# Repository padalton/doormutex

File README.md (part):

# doormutex 🚦

*A mutex for your door.*

**A traffic light for my basement office.** From the hallway the family can see whether it's worth coming downstairs:
🔴 **red** = meeting, please don't disturb · 🟡 **yellow** = working, come in if it's important · 🟢 **green** = come in · ⚫ **off** = not in the office.

The state is detected automatically (microphone/camera, Google Calendar, working hours, screen lock) and can be overridden at any time from a KDE widget, a Stream Deck or the web UI. Open source & open hardware: software, firmware, PCB (KiCad) and a 3D-printed enclosure (OpenSCAD).

> **Status: early development.** This README is the project definition and feature set (as of 2026-10-30). The repo is public from day one so anyone can follow the project as it grows. Software: [`hub/`](hub/) (with web UI), [`companion/`](companion/), [`plasmoid/`](plasmoid/), [`streamdeck/`](streamdeck/).
>
> More documents: [Breadboard prototype & parts list](docs/breadboard.md) · [Wiring the breadboard](docs/wiring.md) · [Development setup](docs/dev-setup.md) · [Google Calendar](docs/google-calendar.md) · [iPhone & Shortcuts](docs/apple-shortcuts.md) · [Android](docs/android.md) · [Hub](hub/README.md) · [API (OpenAPI)](api/openapi.yaml) · [Translating](TRANSLATING.md)

## Signals

One traffic light, three chambers, just like on the road: red on top, yellow in the middle, green at the bottom. The position tells the meaning, even without telling the colours apart.

| Light | State | Meaning | E-ink sign (example) |
|---|---|---|---|
| 🔴 red | `dnd` | Meeting – please don't come in | "Meeting · until 14:30" |
| 🟡 yellow | `working` | Working – only if it's important | "Working · next meeting 15:00" |
| 🟢 green | `free` | Come in! | "Free · next appointment tomorrow 09:00" |
| ⚫ off | `away` | Not in the office (PC locked or off) | "Not in the office" |

**Phases**, modelled on the Austrian road traffic regulations (StVO § 38):

| Light | Phase | When |
|---|---|---|
| 🟢 blinking | **Last call** | before a meeting, coming from green – "quick, I'm in a meeting soon" |
| 🔴 / 🟡 alternating | **Last call from yellow** | before a meeting, coming from yellow. The StVO has no such signal, and blinking yellow is taken by the fault |
| 🔴 + 🟡 | **Ending soon** | before a meeting ends and yellow or green follows. In the StVO, red+yellow means: stop, green is coming |
| 🟡 blinking | **Fault** | hub or Wi-Fi gone, data too old, or the companion went silent without signing off. Blinking yellow means "caution" in the StVO |
| off + "battery empty" | **Battery empty** | cut-off threshold reached |

**Timing:** by default the phases follow the StVO – green blinks four times, yellow shows ≈ 3 s before red, red+yellow ≈ 1–2 s before green. That's authentic, but over in seconds. A switch per phase (config and web UI) turns it into a real warning with a lead time instead, e.g. 3 or 5 minutes.

### E-ink sign

A small e-ink display sits below the light. It shows **absolute times instead of a countdown** ("until 14:30" rather than "23 min left"). So the content only changes when the state changes: no motion sensor needed, no power while idle.

1.54″, 200 × 200 pixels, black and white – rendered by the hub (frames from the tests, actual size). E-ink has no colour, so the status is a big word plus a symbol: ⛔ do not disturb, 🕓 working, ✓ come in, ☾ not here, ⚠ fault. The light already shows the colour; the sign adds the small print, readable right in front of the light.

Content: status, until when, the reason (event kind such as "video call", never a title) or the message, the next free time, the time of the last change and the battery. The frame only changes when its content does, so the panel isn't refreshed for nothing. English and German (per profile, setting `eink_language`).

## Feature set

### Must – v1

- **Traffic light hardware:** three chambers (red/yellow/green), ESP32-C6, Wi-Fi + MQTT, 18650 cell with safe charging electronics, USB-C for charging *and* permanent power
- **E-ink sign:** until when, what's next, reason, battery
- **Enclosure as a miniature traffic light** (OpenSCAD) with a removable wall mount
- **Automatic detection:**
  - microphone or camera in use → red
  - Google Calendar → red or yellow, by rules
  - working hours (incl. Austrian public holidays) → yellow
  - PC locked → off
  - otherwise → green
- **Manual override with duration:** from 15 min to "until end of work day", "until the next automatic change" or indefinite; "auto" resets
- **KDE Plasma widget** (panel and desktop): see the detected state and its reason, override with a time, pomodoro
- **Desktop notification** on every state change
- **Last call** and **failsafe** (see Signals)
- **Home Assistant via MQTT discovery:** state, state-change event, current slot, next free slot, battery
- **Hub as a Docker container** in the homelab

### Should

- **Ending soon** phase (red+yellow)
- **Stream Deck XL** as a control panel
- **Flashing and Wi-Fi setup in the browser** (ESP Web Tools + Improv), OTA updates
- **Automatic brightness** via light sensor, night dimming
- **Battery runtime estimate** in HA
- **Profiles:** several people and lights on one hub, each with its own rules, calendars and tokens
- **Room mode** for people without a PC companion – a teenager's room, the parents' bedroom or living room: controlled by phone (web app, Apple Shortcuts), web UI or Home Assistant, and through HA by voice via Alexa or Google Home (see [Profiles & room mode](#profiles--room-mode))

### Could

- **Matter over Wi-Fi** (uncertified, without the logo): Apple Home, Google Home, Alexa and HA directly, next to MQTT. Matter has no traffic-light device type, so each state becomes an on/off endpoint (mutually exclusive)
- Generic **webhook signals**, e.g. for Claude Code (see below)
- **ESPHome example config** for builds on mains power ("bring your own lamp")
- **Prometheus metrics** and a Grafana dashboard (meeting statistics)
- **Wi-Fi 6 TWT** on the ESP32-C6 for longer battery life, if the router supports it
- Companion for Windows/macOS, GNOME extension
- "Tell me when free" push (ntfy) – for families who don't just text anyway

### Won't – on purpose

| Idea | Why not |
|---|---|
| A second light at the basement door | The decision is made at the top of the stairs – one light is enough |
| Knock button / back channel | The family texts on WhatsApp anyway |
| Dedicated control desk ("signal box") | Stream Deck XL + widget cover it |
| Motion / mmWave sensor on the device | The LEDs stay on (visible from the hallway) and the e-ink only changes with the state. An mmWave sensor (~70–80 mA) would drain the battery in 1–2 days |
| ESP-NOW / Thread / Zigbee | Wi-Fi is good everywhere, MQTT broker and HA exist – Wi-Fi is simpler |
| Countdown on LEDs | too much power – the e-ink shows absolute times |
| Work/private detection via folder paths, VPN etc. | doesn't fit: everything runs on one machine, paths are personal |
| Ready-made HA automations | entities + triggers only; everyone builds their own automations |
| RGB LEDs (WS2812) | real single colours, position encodes meaning; WS2812 draw current even when "off" |

## Architecture

```mermaid
flowchart LR
  subgraph desk["Desk (KDE Plasma)"]
    comp["Companion<br/>mic · camera · lock<br/>notifications"]
    widget["Plasma widget<br/>state · override · pomodoro"]
    deck["Stream Deck XL<br/>OpenDeck plugin"]
  end
  subgraph lab["Homelab (Docker)"]
    hub["Hub<br/>rule engine · API · web UI<br/>e-ink rendering"]
    mqtt[("MQTT broker")]
    ha["Home Assistant"]
  end
  gcal["Google Calendar"] --> hub
  comp -->|signals + heartbeat| hub
  hub -->|state changes| comp
  widget <--> hub
  deck <--> hub
  hub <--> mqtt
  mqtt <--> ha
  mqtt <-->|Wi-Fi| light["🚦 Traffic light at the stairs<br/>ESP32-C6 · e-ink · 18650"]
  ha -.->|your own automation| hue["Hue stair light"]
```

**Principle: smart hub, dumb light.** The hub decides everything – state, phase, blink pattern, e-ink content – and publishes it via MQTT. The light only displays, reports telemetry and switches to "fault" by itself when the hub goes quiet.

| Component | Tech | Job |
|---|---|---|
| Hub | Go, Docker, SQLite | Rule engine, calendar, working hours, REST/SSE API, web UI, MQTT + HA discovery, e-ink rendering |
| Companion | Go, systemd user service | Microphone/camera (PipeWire), screen lock, desktop notifications, OAuth helper |
| Plasma widget | QML (Plasma 6) | State, override, pomodoro |
| Stream Deck plugin | Go, Elgato SDK protocol | Control panel on the Stream Deck XL (OpenDeck, Elgato app) |
| Firmware | C, ESP-IDF | Wi-Fi power saving, MQTT, LEDs, e-ink, battery |
| Project homepage | GitHub Pages (static) + own domain | Required for Google's OAuth branding (description, privacy policy, terms), plus docs, web flasher (ESP Web Tools needs HTTPS) and the OAuth redirect relay. No backend, no user data |
| PCB | KiCad | ESP32-C6, charging, LED and e-ink drivers – assembled by JLCPCB |
| Enclosure | OpenSCAD (plain, Manifold backend) | Miniature traffic light, magnet foot/side plate, later a removable wall mount |

Home Assistant is not a separate component: the hub announces its entities via MQTT discovery and HA picks them up.

**Why Go?** One static binary per component, tiny Docker images, good libraries for MQTT, D-Bus and Google APIs – and the companion can later be cross-compiled for Windows/macOS.

**API first:** the OpenAPI spec in [`api/openapi.yaml`](api/openapi.yaml) is the contract between hub, companion, widget and Stream Deck plugin. A test keeps spec and router in sync.

| Endpoint | Purpose |
|---|---|
| `GET /api/v1/status` | current state incl. reason, slot, next free slot |
| `GET /api/v1/timeline?from=…&to=…` | planned slots from calendar, working hours and timers |
| `PUT` / `DELETE /api/v1/override` | set an override (status + duration or end) / clear it |
| `PUT` / `DELETE /api/v1/pomodoro` | start / stop a pomodoro timer (work phase red by default; setting `pomodoro_work_status` or `work_status` per request for yellow) |
| `POST /api/v1/signals/companion` | companion heartbeat (microphone, camera, lock) and goodbye before shutdown/suspend |
| `POST` / `DELETE /api/v1/signals/{source}` | webhook signals with TTL |
| `GET /api/v1/events` | live updates (Server-Sent Events) |
| `GET /api/v1/profiles` | profiles the token may see, with their state |
| `GET` / `PUT /api/v1/settings` | light per calendar event kind, warning timing (saved, overrides the config) |
| `PUT` / `DELETE /api/v1/message` | e-ink message |
| `GET /api/v1/eink.png`, `GET /api/v1/eink.bin` | the e-ink frame as a preview image / packed for the panel (5000 bytes, SSD1681 layout), with ETag |
| `GET /api/v1/calendar`, `GET /api/v1/history` | calendar account health, recent status changes |

## State logic

Every source contributes a *claim*: status, priority and validity. The best valid claim wins.

| Prio | Source | Result | Details |
|---|---|---|---|
| 1 | Microphone or camera in use | `dnd` | counts after ≥ 10 s (debounce), holds for 2 min (reconnects, chat after the call) |
| 2 | PC locked, shut down or suspended | `away` | the companion signs off; silence without a goodbye is a fault (see below) |
| 3 | Manual override (widget, Stream Deck, web UI, phone, HA) or pomodoro | any | always ends: after a duration, "until the event ends", "until end of work day", "until the next automatic change" – or explicitly indefinite |
| 4 | Calendar event | by event kind | see [Google Calendar](#google-calendar) |
| 5 | Working hours | `working` | weekly plan, public holidays, extra days off |
| 6 | Webhook signals (optional) | usually `working` | with TTL |
| 7 | Default | `free` | – |

- **Microphone/camera beat everything,** including a manual override: a spontaneous Slack or Teams call turns the light red at once. The override isn't cleared and applies again after the call.
- **Microphone/camera beat the lock screen:** nobody locks the PC by hand during a call. But in a meeting where you only listen, you don't touch the mouse, and after a few minutes the screen locks itself. It stays red anyway.
- **Locking beats the override:** a nerd only locks the PC when leaving the desk. The override isn't cleared either; after unlocking it applies again while it's still valid.
- **Heartbeats:** the companion reports every 30 s and signs off on shutdown, suspend and lock (logind). If it is silent for 90 s *without* signing off (crash, killed), the light shows a fault (yellow blinks) until the end of the work day, then off.
- **Public holidays and days off** only remove the working hours. Calendar events still count: PC on with meetings on a holiday → red as usual (holiday workers, self-employed); PC on without events → green; PC off → off.
- **Failsafe on the light:** hub offline (MQTT Last Will) or state too old → yellow blinks.
- **Planning ahead:** the hub knows the future (calendar + working hours). From it, it computes the current slot, the next change and the next free slot – for the e-ink, the widget and HA.
- **Unknown end:** a call without a calendar entry or a locked screen has no known end. Then `until` and `next_free` are `null` instead of a guess. If a calendar meeting is running during a call, the call is assumed to end with the meeting.

## Profiles & room mode

One hub, several **profiles** – one per person and light. Each profile has its own rules, calendars, working hours, MQTT topics and API tokens. A token only controls its own profile: the teenager's phone can't switch the office light.

**Room mode** is a profile without a PC companion and usually without a calendar. It is for everyone who isn't the nerd in the basement: a teenager's room, the parents' bedroom or living room.

- **Controls:** phone, web UI and Home Assistant – and through HA by voice via Alexa or Google Home.
- **No companion required:** the light shows what was set last; when that ends, it falls back to the profile's default (e.g. off).
- **The e-ink shows a short message** ("Gaming until 21:00").
- **The office profile can also run without a companion,** controlled only via HA (light and message) – for setups where the companion can't run.

**Configuration** (see [`hub/config.example.yaml`](hub/config.example.yaml)):

```yaml
profiles:
  - id: office
    mode: office # companion, calendar, working hours
  - id: teen
    name: Teen room
    mode: room # no companion, no working hours, off by default
```

```bash
doormutex-hub token create teen-phone teen               # works only for profile "teen"
doormutex-hub token create widget                        # all profiles, choose with ?profile=
doormutex-hub token create couch teen office --read-only # only looks, never switches
```

The API serves the token's first profile without any extra parameter, so the same client works for every profile. `GET /api/v1/profiles` lists the profiles a token may see, `GET /api/v1/me` its role. A **read-only** token sees the state, the timeline, the history and the event stream, and nothing else – for a phone on the couch or a display in the kitchen. Tokens can also be created in the web UI: *Settings → Add a phone* shows a QR code for the phone.

Where room mode runs for people *without* a homelab (no Docker, no HA) is still open – see [open questions](#open-questions).

## Signal sources

### Companion (Linux)

Implemented in [`companion/`](companion/) – install as a systemd user service, see its README.

- **Microphone:** PipeWire capture streams (`media.class = Stream/Input/Audio`) in state "running". Ignored:
  - level meters (pavucontrol, the Plasma volume applet)
  - recordings of outputs (monitor sources, e.g. screen recording)
  - apps on a configurable ignore list
- **Camera:** open `/dev/video*` devices and PipeWire video streams.
- **Screen lock:** logind `LockedHint` of the user's graphical session (a systemd user service has no session of its own).
- **Goodbye:** before suspend and shutdown (logind delay inhibitor) and when the service stops; silence without a goodbye is a fault.
- **Notifications** on every state change, with the reason ("🔴 microphone in use – Firefox") and quick actions ("wrong detection", "clear override").
- **Reference setup:** CachyOS, KDE Plasma 6 (Wayland), PipeWire.

### Google Calendar

- **Connection:** Google Calendar API (recommended: near real time, provides `eventType`, attendees and conference links) or the secret iCal address (simpler, but sometimes heavily delayed).
- **Several Google accounts per profile,** e.g. private and work: each account has its own sign-in and refresh token, and any number of calendars per account.
- **Mirrored blockers:** in the reference setup HubSpot's "book a meeting" page reads the private calendar, so an Apps Script copies work events into it as blockers (the day job comes first). With both accounts connected the hub would see every work meeting twice. The script therefore marks its copies (`extendedProperties.private`), and the hub ignores marked copies when the source account is connected. If the work account can't be connected (e.g. the employer blocks third-party apps), the script can write the event kind into the mark instead, and the hub reads the kind from the copy.
- **Event kinds and default lights** – the light per kind can be changed in the web UI:

  | Kind | Detected via | Default |
  |---|---|---|
  | Video call | Google Meet: `conferenceData` (`hangoutsMeet`); Zoom, Teams, Webex, Jitsi: conference add-on or link in location/description | 🔴 `dnd` |
  | Focus time | `eventType: focusTime` | 🟡 `working` |
  | Out of office, timed | `eventType: outOfOffice` | 🔴 `dnd` – in the reference setup private appointments are blocked as OOO in the work calendar. If the PC is locked, the light is off anyway |
  | Out of office, all day | `eventType: outOfOffice`, all-day | day off (vacation): no working hours that day |
  | Other event | – | 🟡 `working` – e.g. a phone call on the mobile, which the companion can't see |
  | Tentative | invitation answered "maybe" or not answered yet (`responseStatus` `tentative` / `needsAction`) | 🟡 `working`, whatever the kind – or "like the kind", or ignored |
  | Ignored | working location, birthdays, other all-day events, events marked "free", declined events | – |

- **Overlapping events:** the strictest status wins (`dnd` before `working`), not the one that started last.
- **Calendar and microphone/camera complement each other:** a call known from the calendar gives the last call ahead of time; microphone/camera catch spontaneous calls and always win.
- **Focus time and out of office only exist in Google Workspace accounts** and only on primary calendars – in a private Gmail calendar there are plain events only.
- **Privacy:** location and description are only read to find video links; titles and contents are never stored or shown. Before connecting a work account, check the employer's IT policy.
- **Set-up:** [docs/google-calendar.md](docs/google-calendar.md) – OAuth client, sign-in from the web UI (*Settings → Calendar accounts*, through the redirect relay on doormutex.org) or with `doormutex-companion google login <account>` (browser on the desktop, no copy and paste; `doormutex-hub google login` for headless set-ups), mirrored copies. Refresh tokens are stored encrypted. `GET /api/v1/calendar` shows the health of every account.

#### Google sign-in for self-hosters

Two separate problems:

1. **Long-lived tokens.** While an OAuth app is in "Testing", refresh tokens expire after 7 days. To **publish** the app, the Google Auth Platform requires a complete branding page: homepage, privacy policy, terms of service and an authorized domain. The homepage must describe the app; a bare login page is not enough. For verification by Google you must also prove that you own the domain (Search Console). → **Without a real project homepage there is no long-term operation.**
2. **Redirect.** Every installation runs its hub under a different address, usually without public HTTPS. Web clients need an HTTPS redirect to a public domain. Desktop clients are the exception: they may redirect to loopback (`127.0.0.1`). Google does not allow the device flow ("enter a code on another device") for calendar scopes.

**Plan:**

- **Project homepage with its own domain** (GitHub Pages + custom domain, verified in Search Console): description, logo, screenshots, privacy policy, terms of service, docs and web flasher.
- **Stage 1 – for the reference build:** an own OAuth client whose branding points to the project homepage. It can then be published and the 7-day limit is gone. Until verification Google shows a warning at sign-in and caps unverified apps at 100 users.
- **Stage 2 – for everyone else:** a **shared project OAuth client**, verified by Google. `calendar.events.readonly` is a "sensitive" scope, not a "restricted" one: it needs a justification and a demo video, but no paid security assessment. After that, nobody needs their own Google Cloud console.
  - **Sign-in via the companion:** client type "desktop app", loopback redirect to `127.0.0.1`. Google explicitly does not treat the client secret of installed apps as a secret, so it may live in open-source code.
  - **Sign-in via the web UI without companion:** a **redirect relay** on the homepage, modelled on `my.home-assistant.io` – ✅ built for own clients (a second, "web application" client next to the desktop one). Google redirects to `https://doormutex.org/oauth/`; the static page forwards code and `state` only to the hub this browser started the sign-in from, which it stored locally before (a new hub needs a confirmation). The target never comes from the callback's URL parameters, otherwise the relay would be an open redirect. Still open for the shared client: web clients need the client secret for every token refresh in the hub, so it would be in every installation. To be checked before stage 2 starts.
- **Fallback without OAuth:** the calendar's secret iCal address – without `eventType` and attendees, and Google sometimes updates the feed with a long delay.

### Working hours

Weekly plan (e.g. Mon–Fri 08:00–17:00), public holidays per country (Austria built in), extra days off from the config, vacation and absence from the calendar.

### Webhooks (optional) – e.g. Claude Code

Any tool can set a claim with a TTL via `POST /api/v1/signals/<name>`. Example of a Claude Code hook in `~/.claude/settings.json`:

```json
{
  "hooks": {
    "UserPromptSubmit": [
      {
        "hooks": [
          {
            "type": "command",
            "command": "curl -fsS -m 2 -X POST \"$DOORMUTEX_URL/api/v1/signals/claude\" -H \"Authorization: Bearer $DOORMUTEX_TOKEN\" -d '{\"status\":\"working\",\"ttl\":\"30m\"}' || true"
          }
        ]
      }
    ]
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
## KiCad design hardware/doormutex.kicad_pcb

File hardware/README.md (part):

<!--
SPDX-FileCopyrightText: 2026 The doormutex contributors
SPDX-License-Identifier: CERN-OHL-S-2.0
-->

# Hardware

The KiCad project for PCB v1 (milestone M1b, after the [breadboard prototype](../docs/breadboard.md)): schematic, layout and the JLCPCB order files, all generated by scripts from one netlist. Not built yet. The design has been checked against the data sheets once ([what the review changed](#review-before-the-first-order)); [two things](#check-before-ordering) are left that need the e-paper module in hand and JLCPCB's order page.

## PCB v1

| File | What |
|---|---|
| [`tools/design.py`](tools/design.py) | **the circuit** – every part with its value, LCSC number and the net on each pin. Edit this, not the schematic |
| [`tools/gen_schematic.py`](tools/gen_schematic.py) | writes `doormutex.kicad_sch` from it, runs KiCad's ERC and checks that the exported netlist is exactly the design |
| [`lib/`](lib/) | the JLCPCB parts as a project library: symbols and footprints imported from their LCSC numbers with [easyeda2kicad](https://github.com/uPesy/easyeda2kicad.py), so footprint and placement match what JLCPCB assembles. The 3D models (~40 MB) are not in the repository – the same command with `--full` fetches them into `lib/doormutex.3dshapes/`. [`tools/fix_lib.py`](tools/fix_lib.py) corrects the pin types EasyEDA gets wrong (passive parts marked as inputs) |
| `doormutex.kicad_sch` | generated: one A1 sheet, a block per function, net labels on every pin |
| [`tools/gen_pcb.py`](tools/gen_pcb.py) | the board: outline, 4 layers, every part placed by hand-picked coordinates (`PLACE`), the tracks that carry current laid by hand (`ROUTES`), checks that the antenna, the USB-C opening and the INFO button face outwards |
| [`tools/route_pcb.py`](tools/route_pcb.py) | routes the rest with [Freerouting](https://github.com/freerouting/freerouting) (needs Java 25+) around the hand-laid tracks, ground pours, DRC. Fails on a DRC error, a track below 0.2 mm or a via of the router in or on a surface-mount pad |
| [`tools/check_power.py`](tools/check_power.py) | the copper resistance of every power path, from the tracks and vias; fails above a limit per path (run by `route_pcb.py`) |
| [`tools/export_scad.py`](tools/export_scad.py) | writes every part of the board as a box into [`enclosure/doormutex.scad`](../enclosure/doormutex.scad) for its collision check, and compares the enclosure's board parameters with `gen_pcb.py` |
| [`tools/export_jlc.py`](tools/export_jlc.py) | `production/`: Gerber zip, BOM and CPL for JLCPCB (pad centres and bottom-side rotations the way JLCPCB counts them) |
| `doormutex.kicad_pro`, `doormutex.kicad_dru` | design rules (JLCPCB 4-layer, 0.127 mm), net classes (Power 0.5 mm, USB) |

```bash
python3 hardware/tools/gen_schematic.py      # needs kicad-cli (KiCad 9 or 10)
python3 hardware/tools/gen_pcb.py            # replaces the board – placement lives in PLACE
python3 hardware/tools/route_pcb.py          # Freerouting + DRC (0 errors) + power paths + no vias in pads
python3 hardware/tools/export_scad.py        # the board's parts for the enclosure's collision check
python3 hardware/tools/export_jlc.py         # production/
# a new JLCPCB part (from hardware/, so the 3D model's path is relative to the project):
(cd hardware && easyeda2kicad --full --project-relative --output "$PWD/lib/doormutex" --lcsc_id C2845237)
python3 hardware/tools/fix_lib.py
```

### Blocks

```
USB-C ─► bq24074 (power path) ─► SYS ─┬─► TPS63802 ─► 3V3 ─► ESP32-C6-MINI-1, VEML7700, e-paper
                ▲                     │      ▲ EN from TPS3840: off below 3.0 V on SYS
                │ VBAT                └─► LEDs (resistor + AO3400A per lamp)
18650 ─ 0 Ω (measure) ─ PTC ─ P-MOSFET (reverse polarity) ─┘
   └─ minus: DW01A + FS8205A ─► P_N ─ 20 mΩ ─► GND   (MAX17055 counts across it)
```

| Block | Parts (LCSC) | Notes |
|---|---|---|
| MCU | ESP32-C6-MINI-1-H8, 8 MB (C42403058) | the MINI has no GPIO 10/11: e-paper RST → **GPIO 14**, BUSY → **GPIO 15**. Info button on GPIO 5 (LP, wakes from deep sleep), fuel-gauge alert on GPIO 4. Footprint for a 32.768 kHz crystal on GPIO 0/1, not fitted |
| USB | HRO TYPE-C-31-M-12 (C165948), USBLC6-2SC6 (C7519), 5.1 kΩ on CC | one socket for charging, power and flashing – no more pulling the 3V3 wire to use the console |
| Charger | BQ24074 (C54313) | 887 Ω → 1.0 A charge current, 1.1 kΩ → 1.46 A input limit, NTC 10 k (C13564) at the cell: charging between about 0 and 50 °C. Termination at 100 mA (ITERM open), safety timer about 6 h (47 kΩ at TMR; open it would be 5 h, 4 h at worst – too close to what a worn or large cell needs at 1 A). Four vias in its thermal pad take the heat into the ground plane |
| Cell | Keystone 1042 holder (C5249310), PTC 2 A (C207074), DMP2035U reverse polarity (C110499), DW01A + FS8205A (C351410, C908265) | a 0 Ω in the cell's plus lead (and a 2-pin footprint next to it) to measure the current, e.g. with the INA228 logger |
| Fuel gauge | MAX17055 (C2976422), 20 mΩ sense (C163095) | counts charge (ModelGauge m5) instead of guessing from the voltage like the breadboard's MAX17048, which jumped by 10–20 % on plug-in. Same address 0x36, new driver |
| 3.3 V | TPS63802 (C2845237), 0.47 µH (C668312), TPS3840DL30 (C2862542) | the supervisor drives the buck-boost's EN directly (1 MΩ pull-up): below 3.0 V on SYS everything is off. About 30 µA are left on the cell then – charger 4, its EN2 pull-down 11, fuel gauge 7, protection IC 3, pull-up 3 – until the protection IC opens at 2.5 V. With USB, SYS stays up even with an empty cell |
| Lamps | AO3400A (C20917), XINGLIGHT XL-2012 red/yellow/green (C7371909, C7371908, C965815) | from SYS, two LED places per lamp (the second not fitted). 150 Ω red/yellow, 100 Ω green: at full duty on USB (SYS up to 4.5 V) that is at most 17 mA of the 30 the red and yellow LEDs are rated for, and 19 of the green one's 20. The firmware evens out the falling cell voltage and the colours (LED reference and levels in menuconfig) |
| Sensors, e-paper | VEML7700-TT (C1850416), right-angle JST PH socket S8B-PH-K-S (C157915) for the Waveshare module's cable | the **-TT** reel is the top-view one: the sensor looks away from the board. The -TR reel is the same part placed on its side |
| Buttons | 2 × TS-1187A for RESET/BOOT (C318884), SKRTLAE010 side-actuated INFO at the bottom edge next to USB-C (C110293) | |

### Layout

41 × 191.5 mm, 4 layers (inner layer 2, right below the parts on the back, a solid ground plane; inner layer 1 for routing), the board is the back wall of the three chambers in the enclosure's PCB build (`build = "pcb"` in [`enclosure/doormutex.scad`](../enclosure/doormutex.scad)).

| Side | What |
|---|---|
| Front (towards the lenses) | the LED pairs in the middle of each reflector cone, the light sensor in the top corner of the green chamber (a pinhole and a hood in the front shell), the e-paper socket in the sign, and a 2 mm wide 3.3 V track from the buck-boost up to the ESP32 |
| Back | ESP32-C6 at the top with its antenna past the top edge (plastic-only roof), the 18650 holder in the middle, lamp drivers left of it, cell protection, sense resistor and fuel gauge right of its minus end, the cell's plus lead (0 Ω, PTC, reverse-polarity MOSFET) below it on the left on its way to the charger, buck-boost and supervisor at the bottom right, USB-C and the side-actuated INFO button on the bottom edge |

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
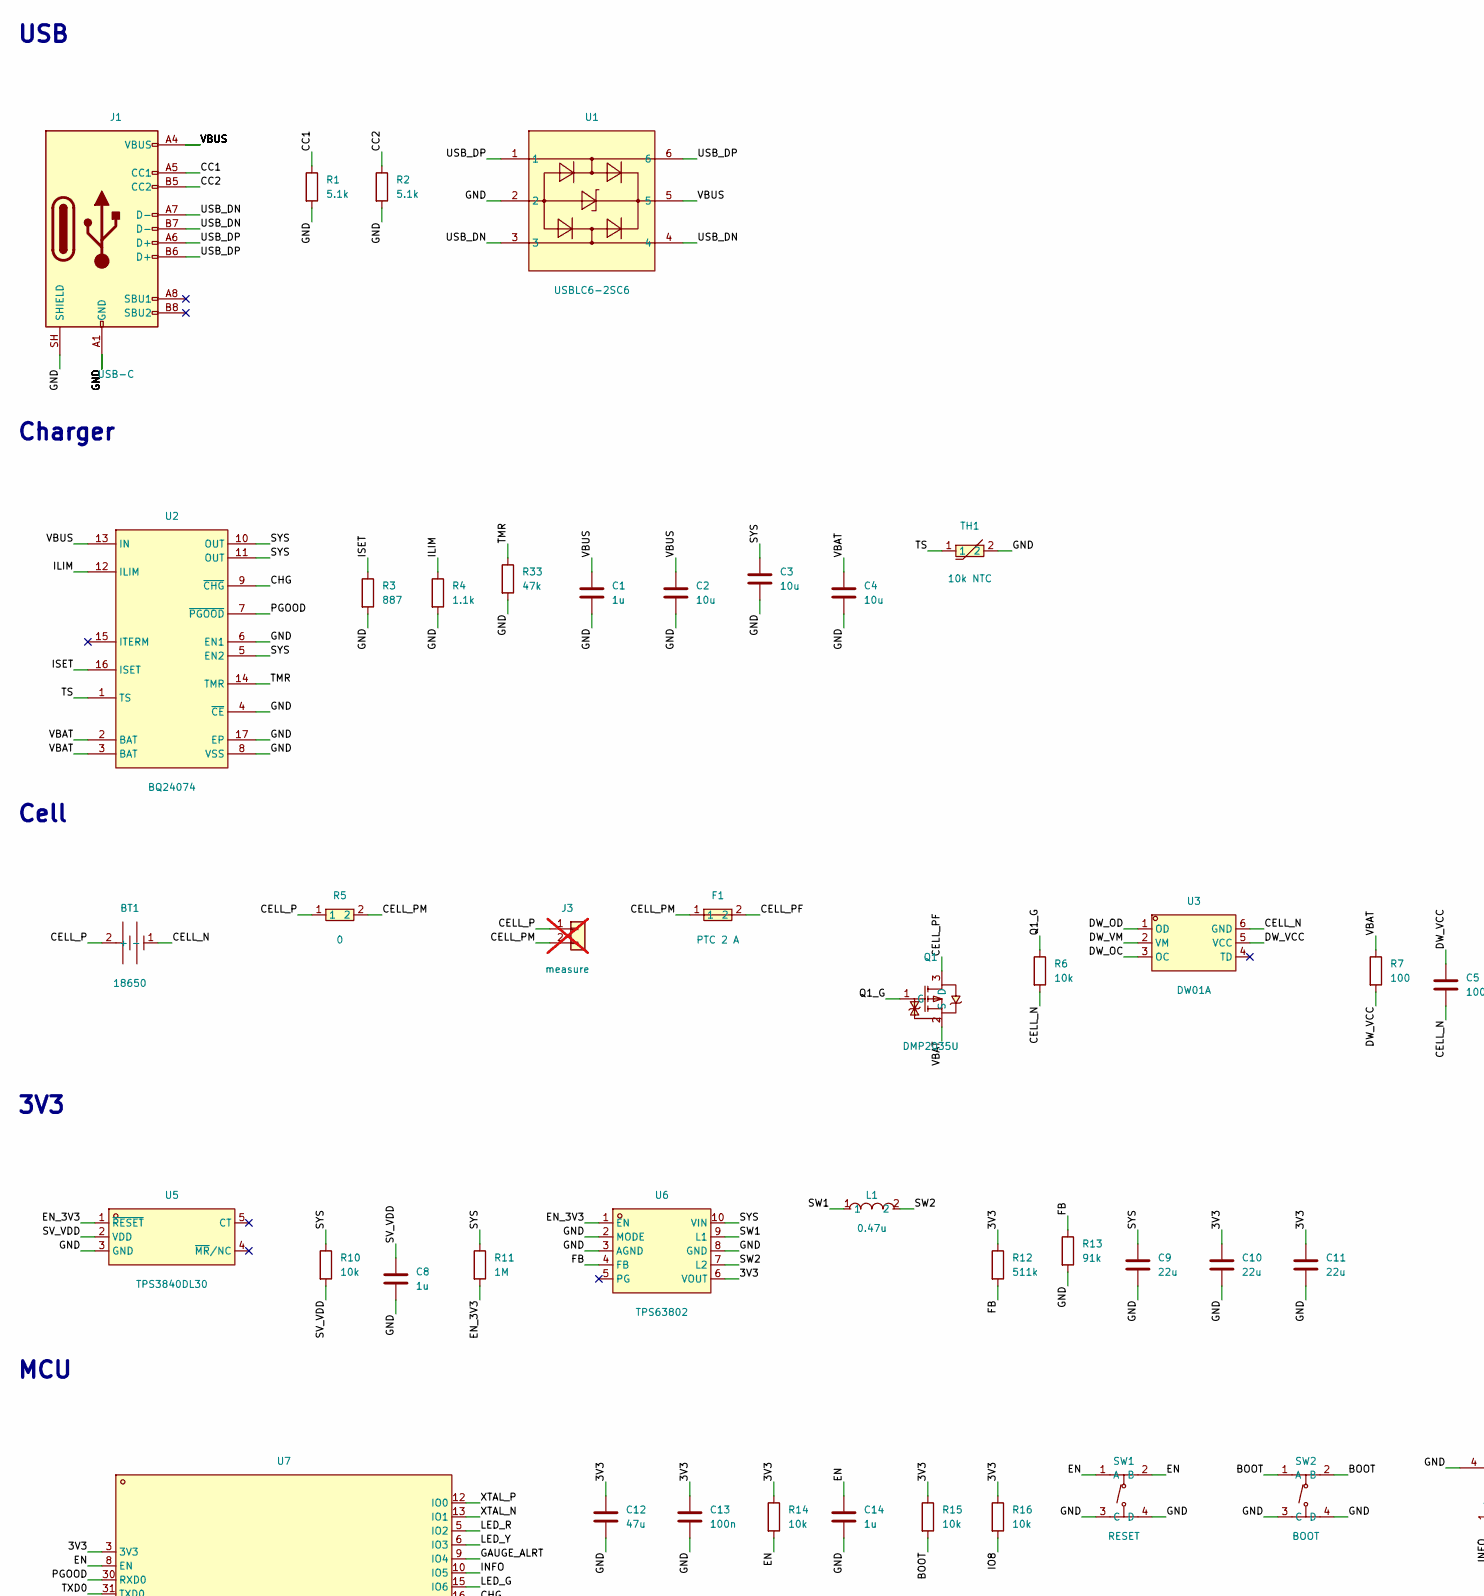
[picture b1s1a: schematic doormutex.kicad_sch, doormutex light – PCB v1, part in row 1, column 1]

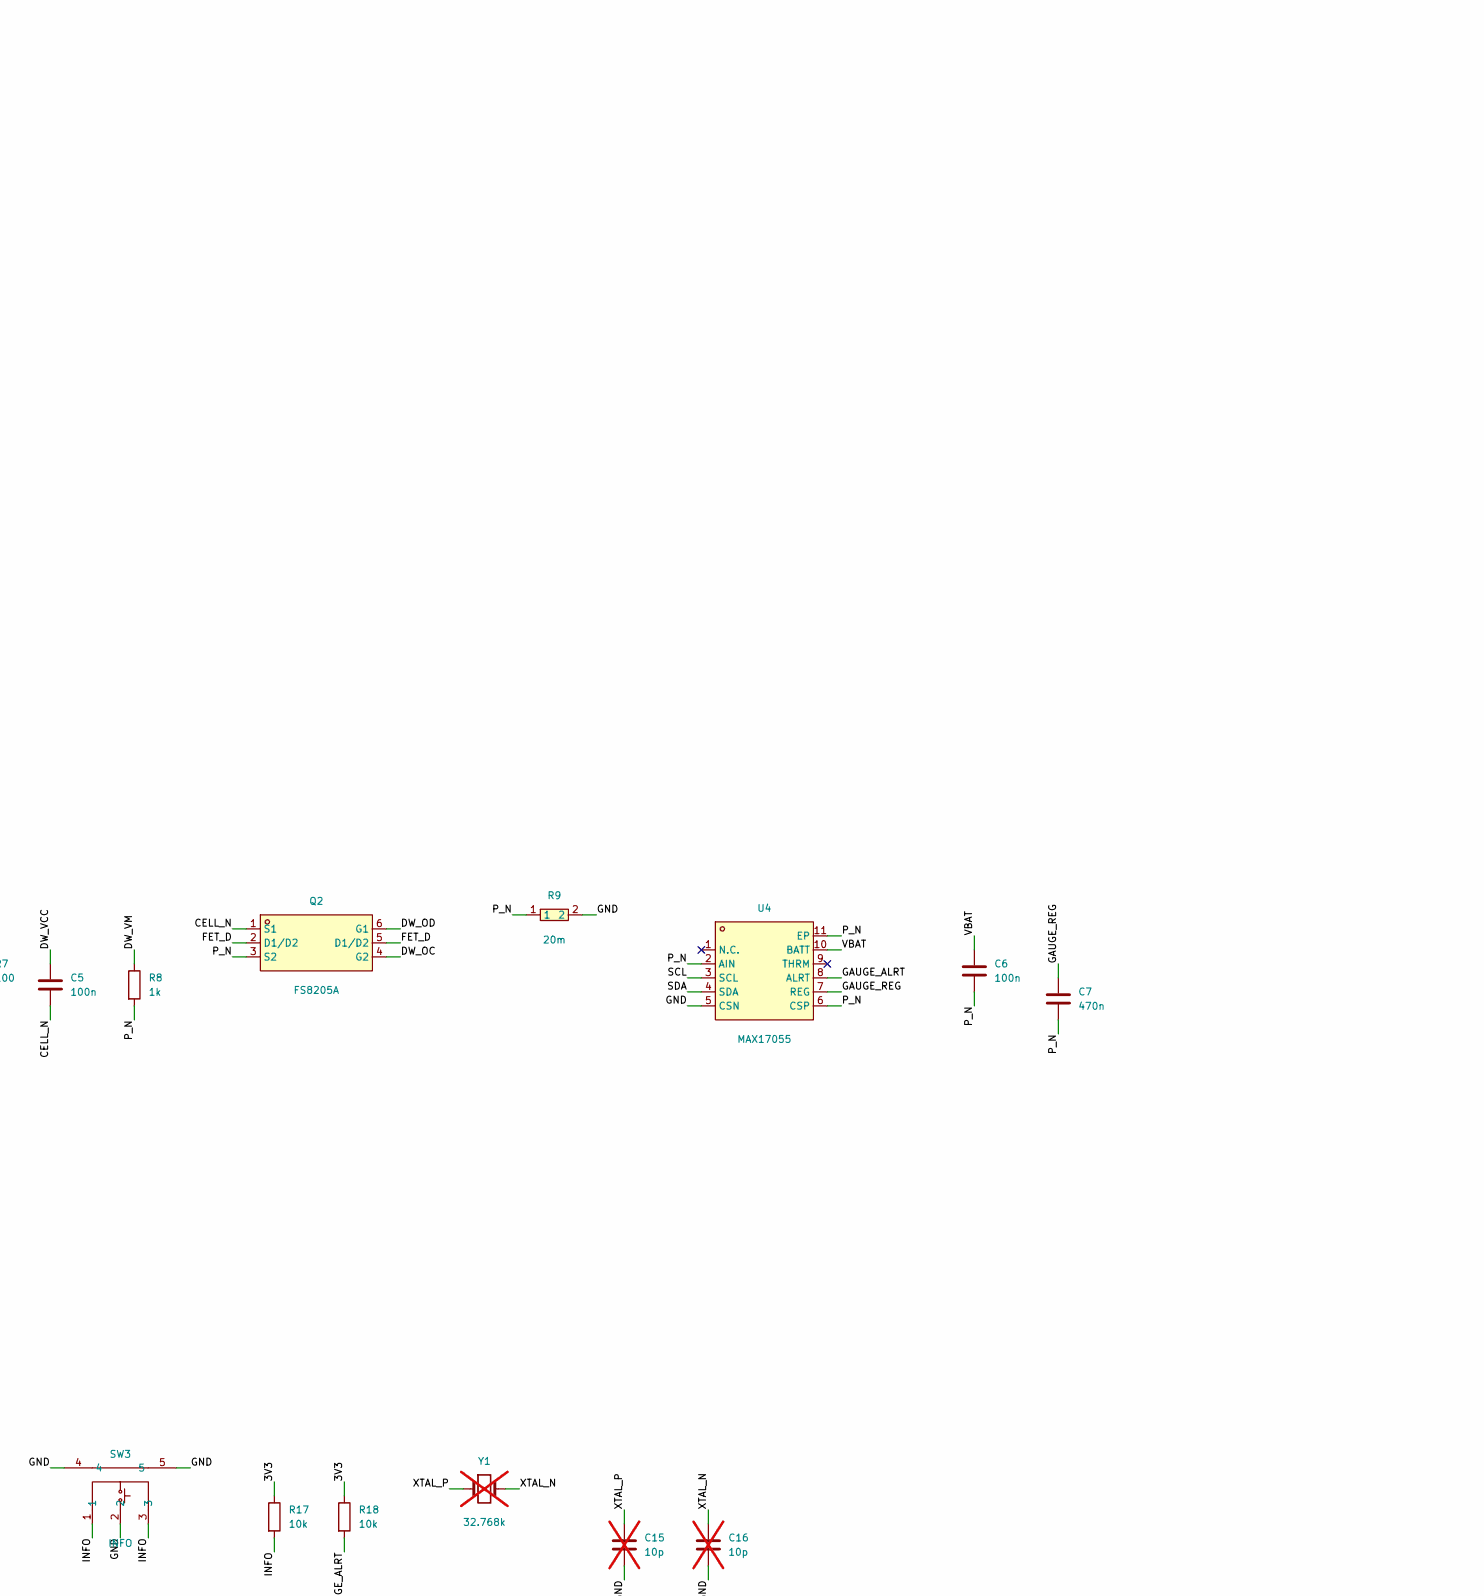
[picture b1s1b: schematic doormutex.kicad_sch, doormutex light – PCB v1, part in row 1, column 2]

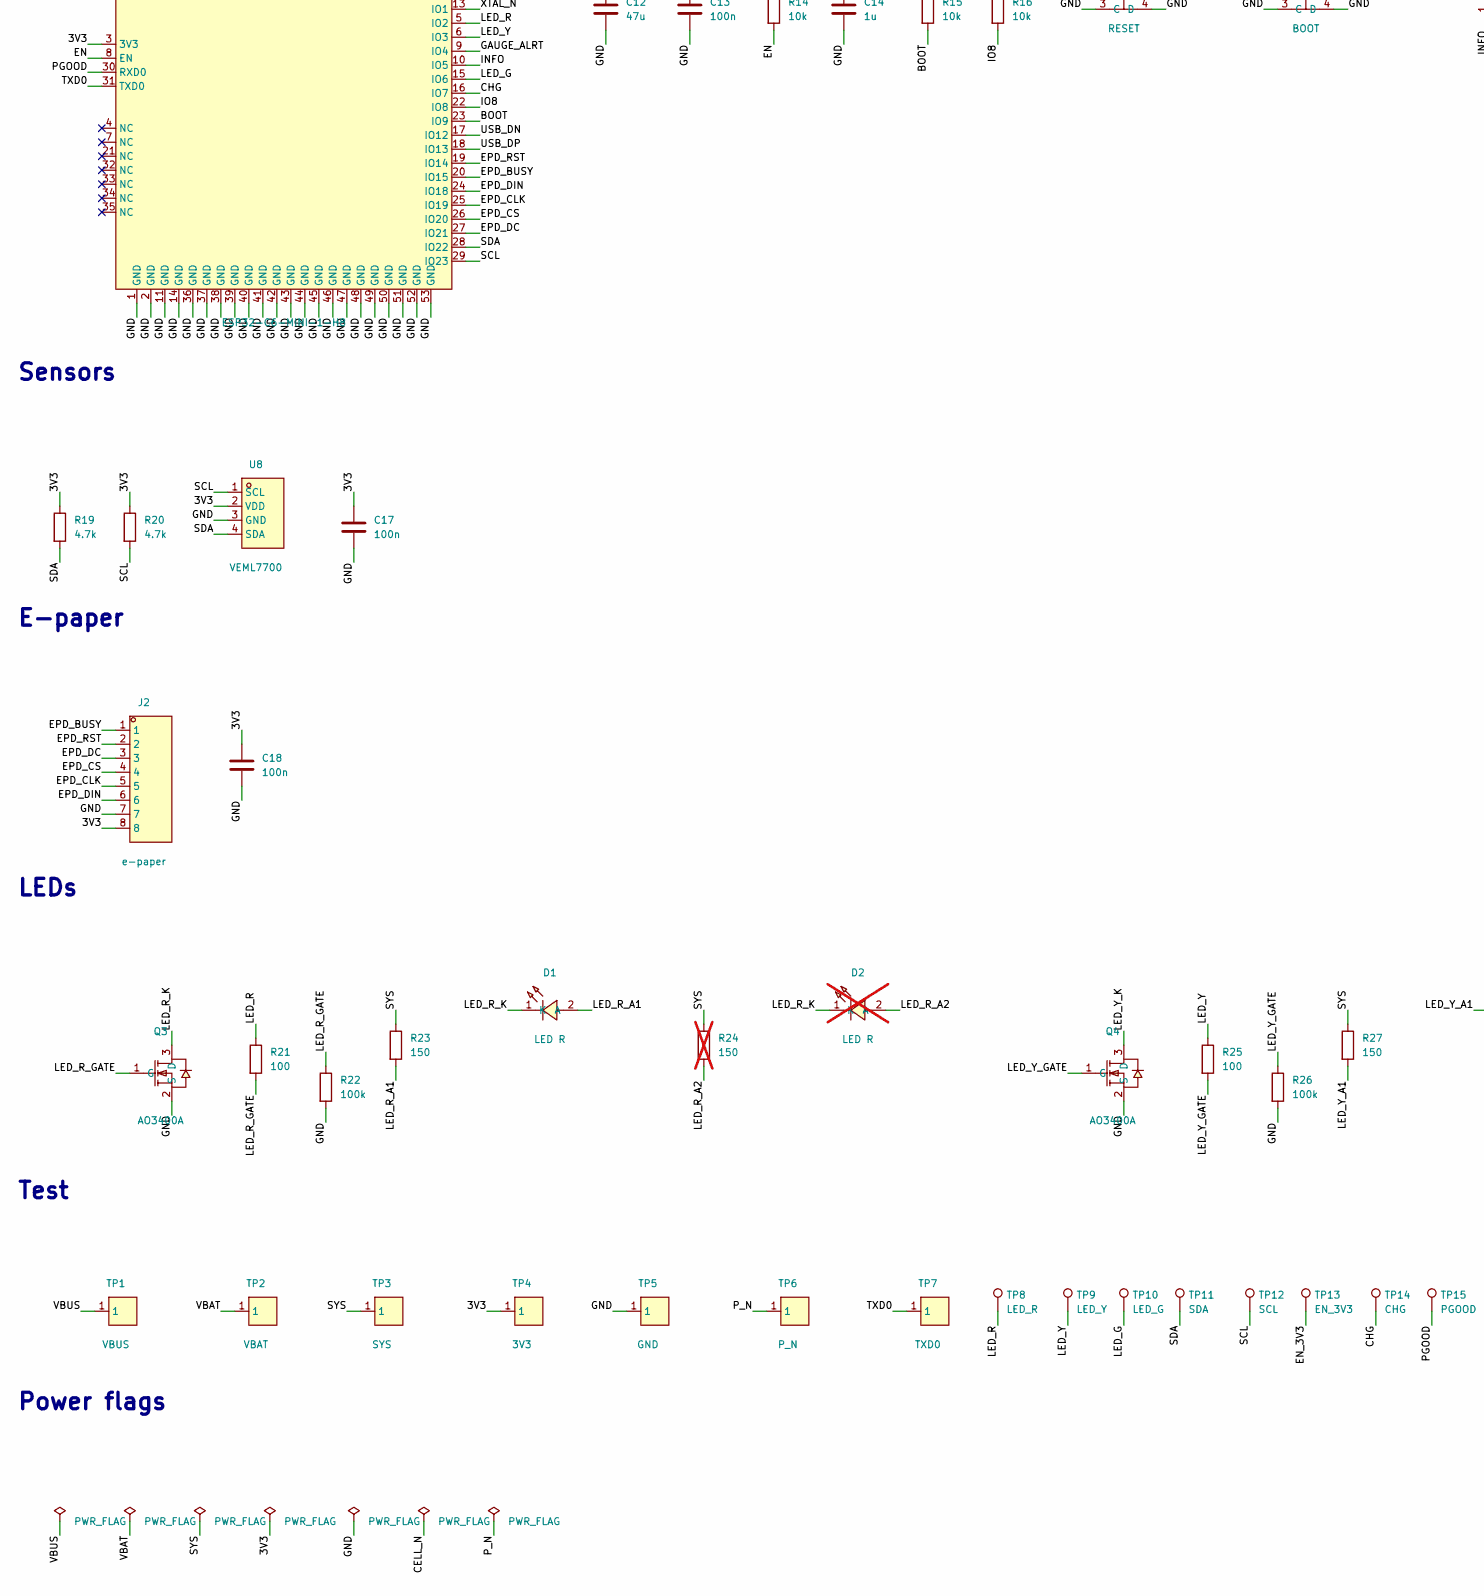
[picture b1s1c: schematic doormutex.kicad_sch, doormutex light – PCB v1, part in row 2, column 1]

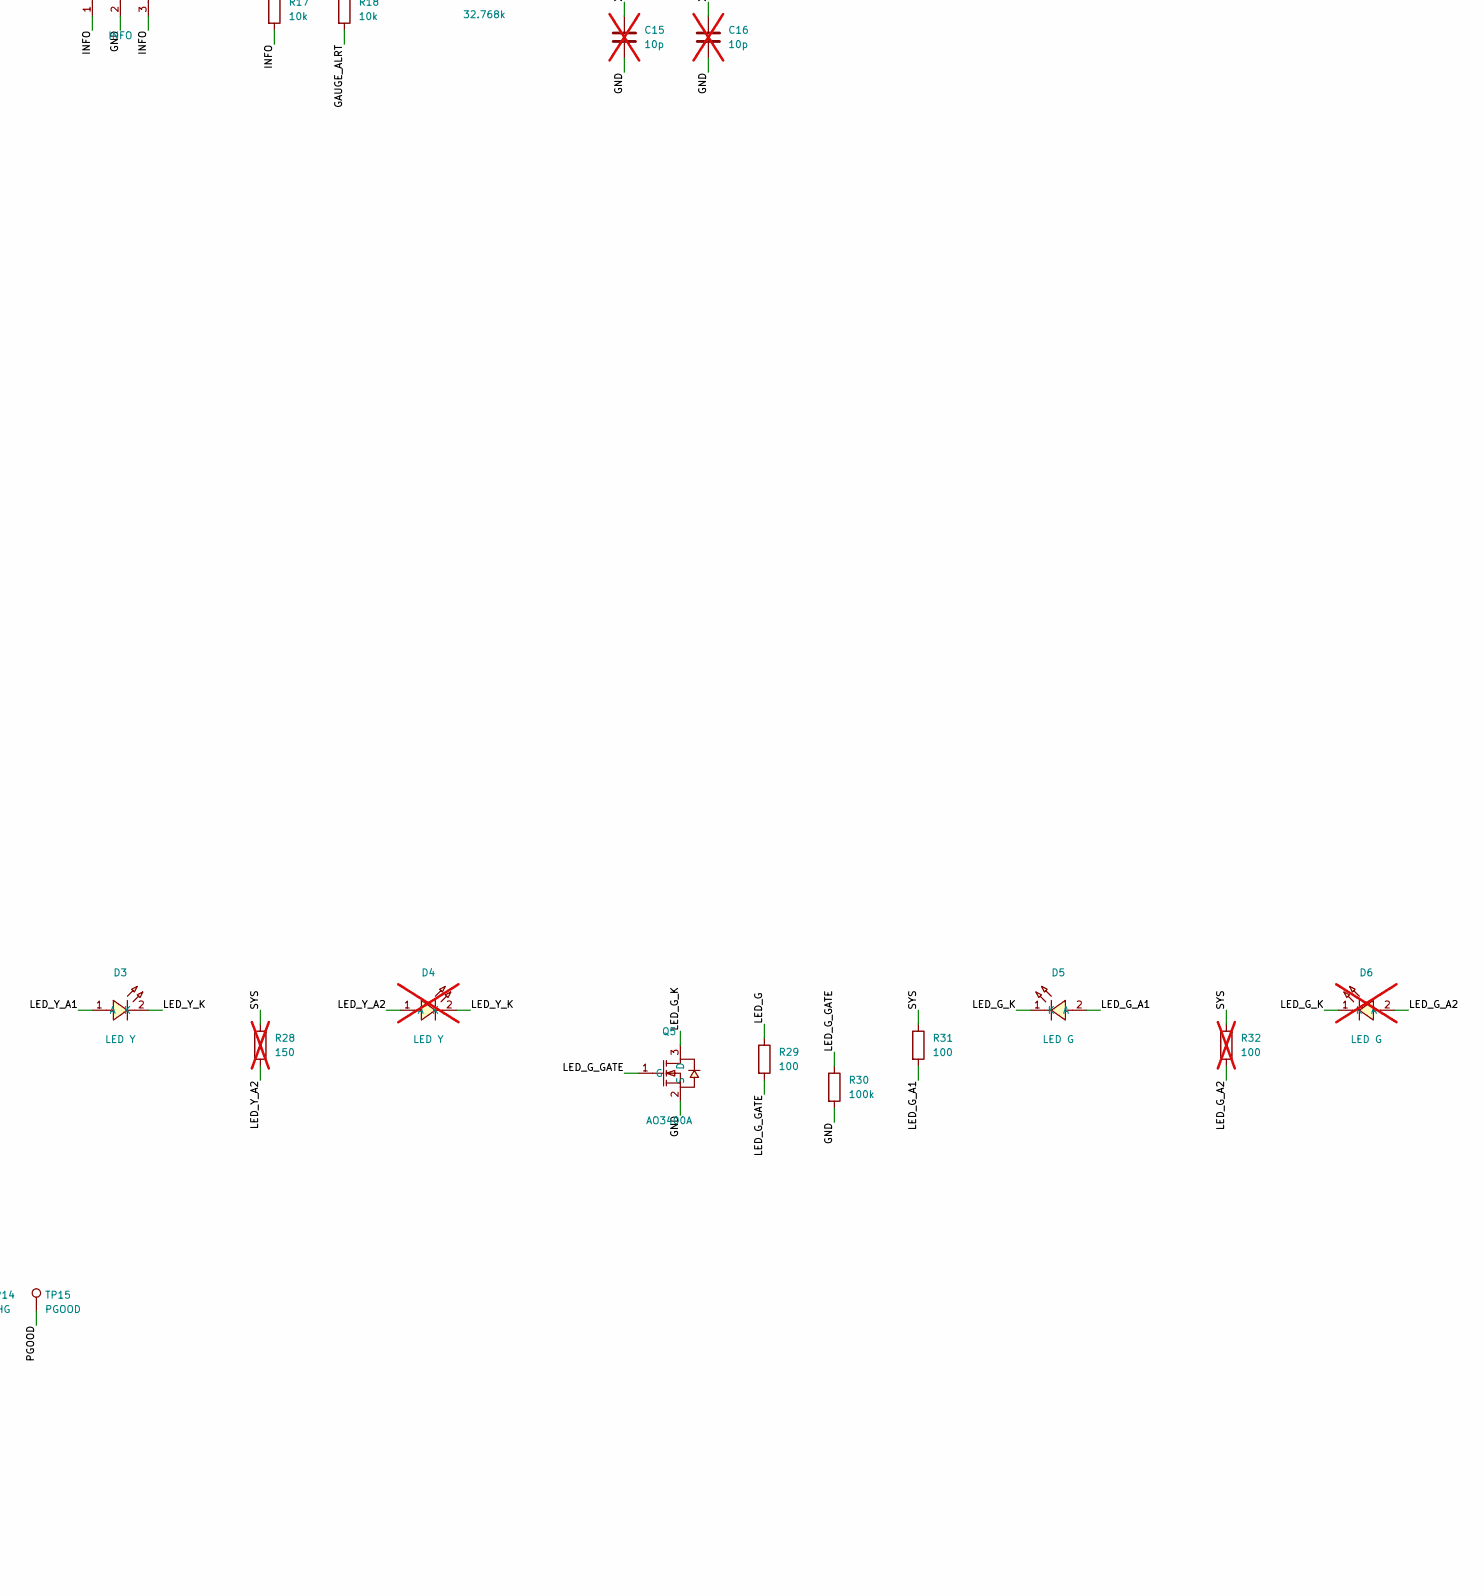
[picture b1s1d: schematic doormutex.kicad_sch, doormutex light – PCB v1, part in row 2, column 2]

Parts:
BT1: 18650; BAT-SMD_1042P; LCSC C5249310
C1, C8, C14: 1u; C_0402_1005Metric; LCSC C52923
C2, C3, C4: 10u; C_0603_1608Metric; LCSC C19702
C5, C6, C13, C17, C18: 100n; C_0402_1005Metric; LCSC C1525
C7: 470n; C_0402_1005Metric; LCSC C47339
C9, C10, C11: 22u; C_0603_1608Metric; LCSC C59461
C12: 47u; C_0805_2012Metric; LCSC C16780
C15, C16: 10p; C_0402_1005Metric; LCSC C32949; not fitted
D1: LED R; LED0805-RD_RED_XL-2012SURC-FJ; LCSC C7371909
D2: LED R; LED0805-RD_RED_XL-2012SURC-FJ; LCSC C7371909; not fitted
D3: LED Y; LED-SMD_L2.0-W1.3_XL-2012UYC-FJ; LCSC C7371908
D4: LED Y; LED-SMD_L2.0-W1.3_XL-2012UYC-FJ; LCSC C7371908; not fitted
D5: LED G; LED0805-RD_GREEN; LCSC C965815
D6: LED G; LED0805-RD_GREEN; LCSC C965815; not fitted
F1: PTC 2 A; F1812; LCSC C207074
J1: USB-C; USB_C_Receptacle_HRO_TYPE-C-31-M-12; LCSC C165948
J2: e-paper; CONN-TH_S8B-PH-K-S-LF-SN; LCSC C157915
J3: measure; PinHeader_1x02_P2.54mm_Vertical; not fitted
L1: 0.47u; IND-SMD_L2.0-W1.6-1; LCSC C668312
Q1: DMP2035U; SOT-23-3_L2.9-W1.6-P1.90-LS2.8-BR; LCSC C110499
Q2: FS8205A; SOT-23-6_L2.9-W1.6-P0.95-LS2.8-BR; LCSC C908265
Q3, Q4, Q5: AO3400A; SOT-23-3_L2.9-W1.3-P1.90-LS2.4-BR; LCSC C20917
R1, R2: 5.1k; R_0402_1005Metric; LCSC C25905
R3: 887; R_0402_1005Metric; LCSC C474137
R4: 1.1k; R_0402_1005Metric; LCSC C25860
R5: 0; R1206; LCSC C17888
R6, R10, R14, R15, R16, R17, R18: 10k; R_0402_1005Metric; LCSC C25744
R7, R21, R25, R29, R31: 100; R_0402_1005Metric; LCSC C25076
R8: 1k; R_0402_1005Metric; LCSC C11702
R9: 20m; R0805; LCSC C163095
R11: 1M; R_0402_1005Metric; LCSC C26083
R12: 511k; R_0402_1005Metric; LCSC C64042
R13: 91k; R_0402_1005Metric; LCSC C4147
R19, R20: 4.7k; R_0402_1005Metric; LCSC C25900
R22, R26, R30: 100k; R_0402_1005Metric; LCSC C25741
R23, R27: 150; R_0402_1005Metric; LCSC C25082
R24, R28: 150; R_0402_1005Metric; LCSC C25082; not fitted
R32: 100; R_0402_1005Metric; LCSC C25076; not fitted
R33: 47k; R_0402_1005Metric; LCSC C25792
SW1: RESET; SW-SMD_4P-L5.1-W5.1-P3.70-LS6.5-TL_H1.5; LCSC C318884
SW2: BOOT; SW-SMD_4P-L5.1-W5.1-P3.70-LS6.5-TL_H1.5; LCSC C318884
SW3: INFO; KEY-SMD_SKRTLAE010; LCSC C110293
TH1: 10k NTC; R0603; LCSC C13564
TP1: VBUS; SMD_RH-5015; LCSC C5199798
TP2: VBAT; SMD_RH-5015; LCSC C5199798
TP3: SYS; SMD_RH-5015; LCSC C5199798
TP4: 3V3; SMD_RH-5015; LCSC C5199798
TP5: GND; SMD_RH-5015; LCSC C5199798
TP6: P_N; SMD_RH-5015; LCSC C5199798
TP7: TXD0; SMD_RH-5015; LCSC C5199798
TP8: LED_R; TestPoint_Pad_D2.0mm
TP9: LED_Y; TestPoint_Pad_D2.0mm
TP10: LED_G; TestPoint_Pad_D2.0mm
TP11: SDA; TestPoint_Pad_D1.5mm
TP12: SCL; TestPoint_Pad_D1.5mm
TP13: EN_3V3; TestPoint_Pad_D1.5mm
TP14: CHG; TestPoint_Pad_D1.5mm
TP15: PGOOD; TestPoint_Pad_D1.5mm
U1: USBLC6-2SC6; SOT-23-6_L2.9-W1.6-P0.95-LS2.8-BL; LCSC C7519
U2: BQ24074; QFN-16_L3.0-W3.0-P0.50-TL-EP1.7; LCSC C54313
U3: DW01A; SOT-23-6_L2.9-W1.6-P0.95-LS2.8-BL; LCSC C351410
U4: MAX17055; TDFN-10_L2.5-W2.0-P0.40-BL-EP; LCSC C2976422
U5: TPS3840DL30; SOT-23-5_L3.0-W1.7-P0.95-LS2.8-BR; LCSC C2862542
U6: TPS63802; VSON-10_L3.0-W2.0-P0.50-TL; LCSC C2845237
U7: ESP32-C6-MINI-1-H8; WIFIM-SMD_61P-L16.6-W13.2-P0.80-ESP32-C6-MINI-1-N4; LCSC C42403058
U8: VEML7700; SENSOR-SMD_EML7700-TT; LCSC C1850416
Y1: 32.768k; Crystal_SMD_3215-2Pin_3.2x1.5mm; not fitted

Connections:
3V3: C10.1, C11.1, C12.1, C13.1, C17.1, C18.1, J2.8, R12.1, R14.1, R15.1, R16.1, R17.1, R18.1, R19.1, R20.1, TP4.1, U6.6 (VOUT), U7.3 (3V3), U8.2 (VDD)
BOOT: R15.2, SW2.1 (A), SW2.2 (B), U7.23 (IO9)
CC1: J1.A5 (CC1), R1.1
CC2: J1.B5 (CC2), R2.1
CELL_N: BT1.1 (-), C5.2, Q2.1 (S1), R6.2, U3.6 (GND)
CELL_P: BT1.2 (+), J3.1, R5.1
CELL_PF: F1.2, Q1.3 (D)
CELL_PM: F1.1, J3.2, R5.2
CHG: TP14.1, U2.9 (~CHG), U7.16 (IO7)
DW_OC: Q2.4 (G2), U3.3 (OC)
DW_OD: Q2.6 (G1), U3.1 (OD)
DW_VCC: C5.1, R7.2, U3.5 (VCC)
DW_VM: R8.1, U3.2 (VM)
EN: C14.1, R14.2, SW1.1 (A), SW1.2 (B), U7.8 (EN)
EN_3V3: R11.2, TP13.1, U5.1 (~RESET), U6.1 (EN)
EPD_BUSY: J2.1, U7.20 (IO15)
EPD_CLK: J2.5, U7.25 (IO19)
EPD_CS: J2.4, U7.26 (IO20)
EPD_DC: J2.3, U7.27 (IO21)
EPD_DIN: J2.6, U7.24 (IO18)
EPD_RST: J2.2, U7.19 (IO14)
FB: R12.2, R13.1, U6.4 (FB)
FET_D: Q2.2 (D1/D2), Q2.5 (D1/D2)
GAUGE_ALRT: R18.2, U4.8 (ALRT), U7.9 (IO4)
GAUGE_REG: C7.1, U4.7 (REG)
GND: C1.2, C2.2, C3.2, C4.2, C8.2, C9.2, C10.2, C11.2, C12.2, C13.2, C14.2, C15.2, C16.2, C17.2, C18.2, J1.A1 (GND), J1.A12 (GND), J1.B1 (GND), J1.B12 (GND), J1.SH (SHIELD), J2.7, Q3.2 (S), Q4.2 (S), Q5.2 (S), R1.2, R2.2, R3.2, R4.2, R9.2, R13.2, R22.2, R26.2, R30.2, R33.2, SW1.3 (C), SW1.4 (D), SW2.3 (C), SW2.4 (D), SW3.2, SW3.4, SW3.5, TH1.2, TP5.1, U1.2, U2.4 (~CE), U2.6 (EN1), U2.8 (VSS), U2.17 (EP), U4.5 (CSN), U5.3 (GND), U6.2 (MODE), U6.3 (AGND), U6.8 (GND), U7.1 (GND), U7.2 (GND), U7.11 (GND), U7.14 (GND), U7.36 (GND), U7.37 (GND), U7.38 (GND), U7.39 (GND), U7.40 (GND), U7.41 (GND), U7.42 (GND), U7.43 (GND), U7.44 (GND), U7.45 (GND), U7.46 (GND), U7.47 (GND), U7.48 (GND), U7.49 (GND), U7.50 (GND), U7.51 (GND), U7.52 (GND), U7.53 (GND), U8.3 (GND)
ILIM: R4.1, U2.12 (ILIM)
INFO: R17.2, SW3.1, SW3.3, U7.10 (IO5)
IO8: R16.2, U7.22 (IO8)
ISET: R3.1, U2.16 (ISET)
LED_G: R29.1, TP10.1, U7.15 (IO6)
LED_G_A1: D5.2 (A), R31.2
LED_G_A2: D6.2 (A), R32.2
LED_G_GATE: Q5.1 (G), R29.2, R30.1
LED_G_K: D5.1 (K), D6.1 (K), Q5.3 (D)
LED_R: R21.1, TP8.1, U7.5 (IO2)
LED_R_A1: D1.2 (A), R23.2
LED_R_A2: D2.2 (A), R24.2
LED_R_GATE: Q3.1 (G), R21.2, R22.1
LED_R_K: D1.1 (K), D2.1 (K), Q3.3 (D)
LED_Y: R25.1, TP9.1, U7.6 (IO3)
LED_Y_A1: D3.1 (A), R27.2
LED_Y_A2: D4.1 (A), R28.2
LED_Y_GATE: Q4.1 (G), R25.2, R26.1
LED_Y_K: D3.2 (K), D4.2 (K), Q4.3 (D)
PGOOD: TP15.1, U2.7 (~PGOOD), U7.30 (RXD0)
P_N: C6.2, C7.2, Q2.3 (S2), R8.2, R9.1, TP6.1, U4.2 (AIN), U4.6 (CSP), U4.11 (EP)
Q1_G: Q1.1 (G), R6.1
SCL: R20.2, TP12.1, U4.3 (SCL), U7.29 (IO23), U8.1 (SCL)
SDA: R19.2, TP11.1, U4.4 (SDA), U7.28 (IO22), U8.4 (SDA)
SV_VDD: C8.1, R10.2, U5.2 (VDD)
SW1: L1.1, U6.9 (L1)
SW2: L1.2, U6.7 (L2)
SYS: C3.1, C9.1, R10.1, R11.1, R23.1, R24.1, R27.1, R28.1, R31.1, R32.1, TP3.1, U2.5 (EN2), U2.10 (OUT), U2.11 (OUT), U6.10 (VIN)
TMR: R33.1, U2.14 (TMR)
TS: TH1.1, U2.1 (TS)
TXD0: TP7.1, U7.31 (TXD0)
USB_DN: J1.A7 (D-), J1.B7 (D-), U1.3, U1.4, U7.17 (IO12)
USB_DP: J1.A6 (D+), J1.B6 (D+), U1.1, U1.6, U7.18 (IO13)
VBAT: C4.1, C6.1, Q1.2 (S), R7.1, TP2.1, U2.2 (BAT), U2.3 (BAT), U4.10 (BATT)
VBUS: C1.1, C2.1, J1.A4 (VBUS), J1.A9 (VBUS), J1.B4 (VBUS), J1.B9 (VBUS), TP1.1, U1.5, U2.13 (IN)
XTAL_N: C16.1, U7.13 (IO1), Y1.2
XTAL_P: C15.1, U7.12 (IO0), Y1.1

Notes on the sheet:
USB
Charger
Cell
3V3
MCU
Sensors
E-paper
LEDs
Test
Power flags

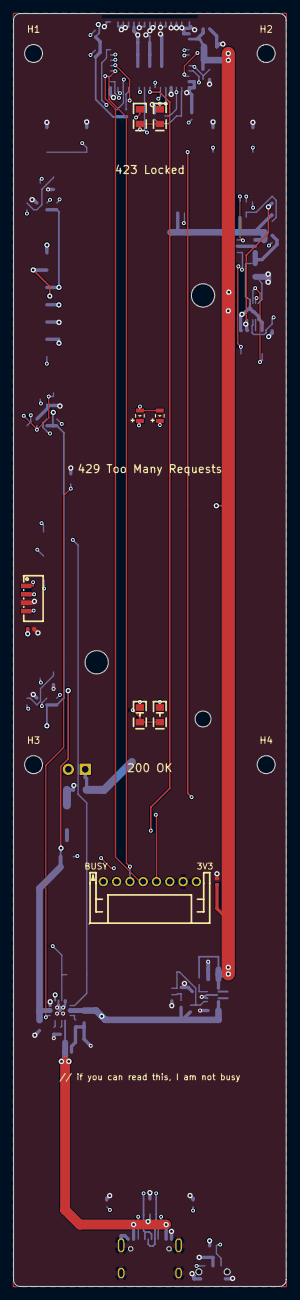
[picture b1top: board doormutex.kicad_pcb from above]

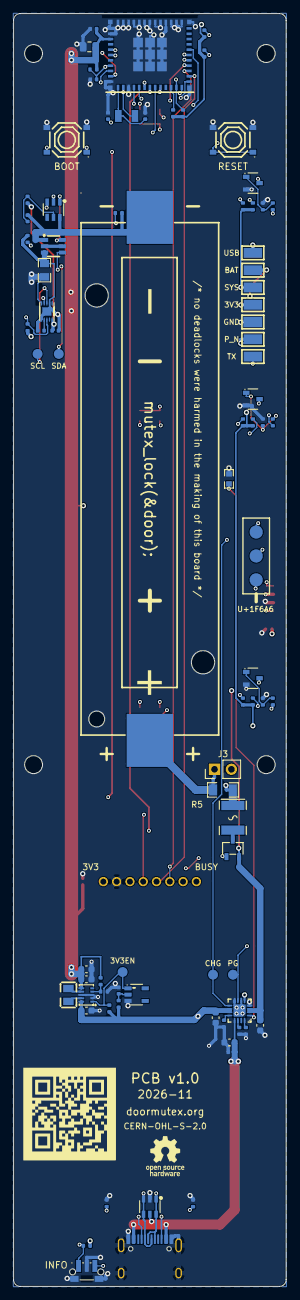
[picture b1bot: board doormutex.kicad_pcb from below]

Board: 4 copper layers, 41.0 x 191.5 mm, 101 parts (87 on the bottom side), 63 nets.

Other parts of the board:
G1: OSHW-Logo_5.7x6mm_SilkScreen
H1, H2, H3, H4: MountingHole_2.7mm_M2.5

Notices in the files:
README.md:
- hardware and enclosure: [CERN-OHL-S-2.0](LICENSES/CERN-OHL-S-2.0.txt)
- docs and photos: [CC BY-SA 4.0](LICENSES/CC-BY-SA-4.0.txt)
ependencies so far are permissive (Go modules: BSD-3, MIT/Apache-2.0, Paho under EPL-2.0/EDL-1.0; ESP-IDF: Apache-2.0; BOSL2: BSD-2; KiCad libraries: CC BY-SA with an exception for designs).
2026-10-29 | Goal for the licence: no commercial redistribution by others (superseded below) | keeps the option to sell it later
